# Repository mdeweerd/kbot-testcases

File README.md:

The Makefile is executed in the docker environment as follows:

Using the `setsoft/kicad_auto:dev_k6` image:

```shell
docker compose run --rm dev_k6
```

Using the `setsoft/kicad_auto_test:dev_k6` image:

```shell
docker compose run --rm dev_k7
```

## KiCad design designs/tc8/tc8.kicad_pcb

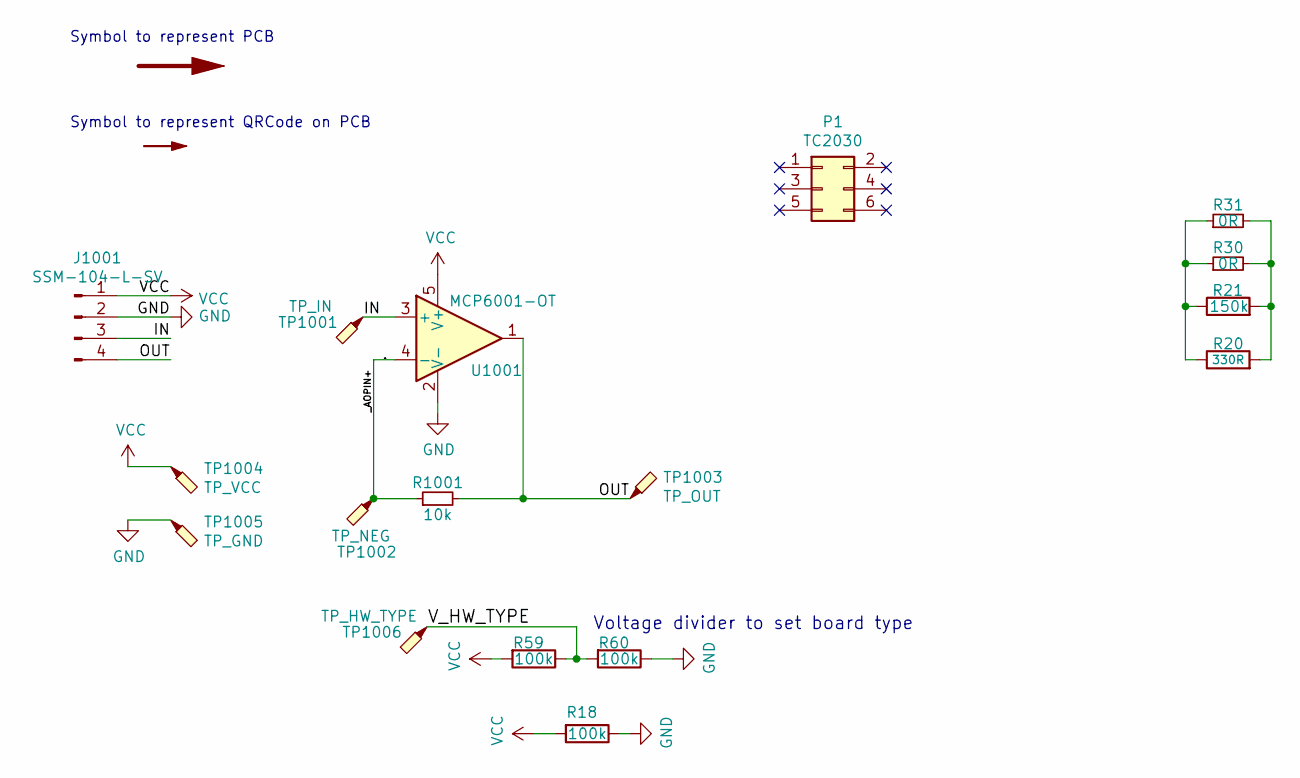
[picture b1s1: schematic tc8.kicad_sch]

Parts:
BRD1: SYM_Arrow_XLarge; biggerPCB
J1001: SSM-104-L-SV; PinSocket_1x04_P2.54mm_Vertical_SMD_Pin1Left
P1: TC2030; TC2030-MCP-FP
QR1: Product QR Code; TC5
R18, R59, R60: 100k; R_0603_1608Metric
R20: 330R; R_0805_2012Metric
R21: 150k; R_0805_2012Metric
R30, R31: 0R; R_0805_2012Metric
R1001: 10k; R_0805_2012Metric
TP1001: TP_IN; TestPoint_Pad_D1.5mm
TP1002: TP_NEG; TestPoint_Pad_D1.5mm
TP1003: TP_OUT; TestPoint_Pad_D1.5mm
TP1004: TP_VCC; TestPoint_Pad_D1.5mm
TP1005: TP_GND; TestPoint_Pad_D1.5mm
TP1006: TP_HW_TYPE; TestPoint_Pad_D1.5mm
U1001: MCP6001-OT; SOT-23-5

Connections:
/IN: J1001.3, TP1001.1, U1001.3 (+)
/OUT: J1001.4, R1001.2, TP1003.1, U1001.1
/V_HW_TYPE: R59.1, R60.2, TP1006.1
/_AOPIN+: R1001.1, TP1002.1, U1001.4 (-)
GND: J1001.2, R18.1, R60.1, TP1005.1, U1001.2 (V-)
unnamed: R20.1, R21.1, R30.1, R31.1
unnamed: R20.2, R21.2, R30.2, R31.2
VCC: J1001.1, R18.2, R59.2, TP1004.1, U1001.5 (V+)

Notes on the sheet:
Voltage divider to set board type
Symbol to represent QRCode on PCB
Symbol to represent PCB

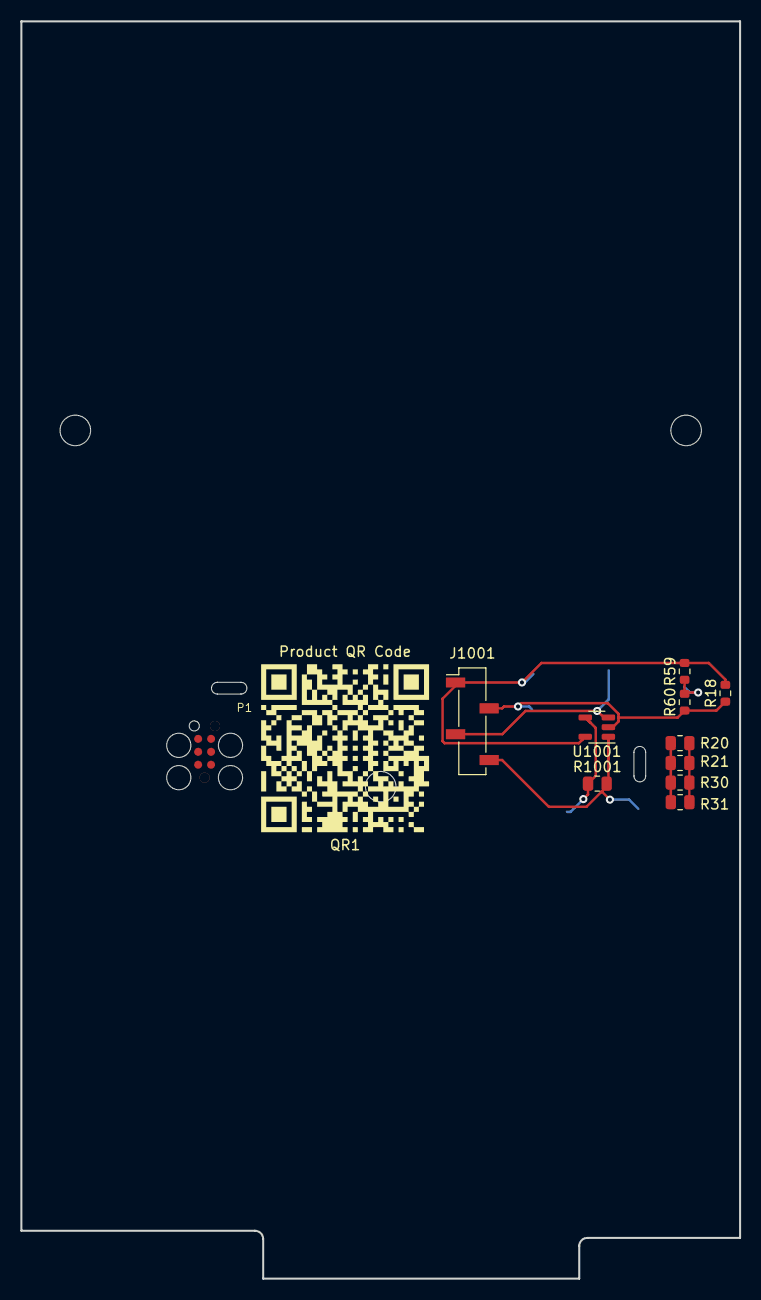
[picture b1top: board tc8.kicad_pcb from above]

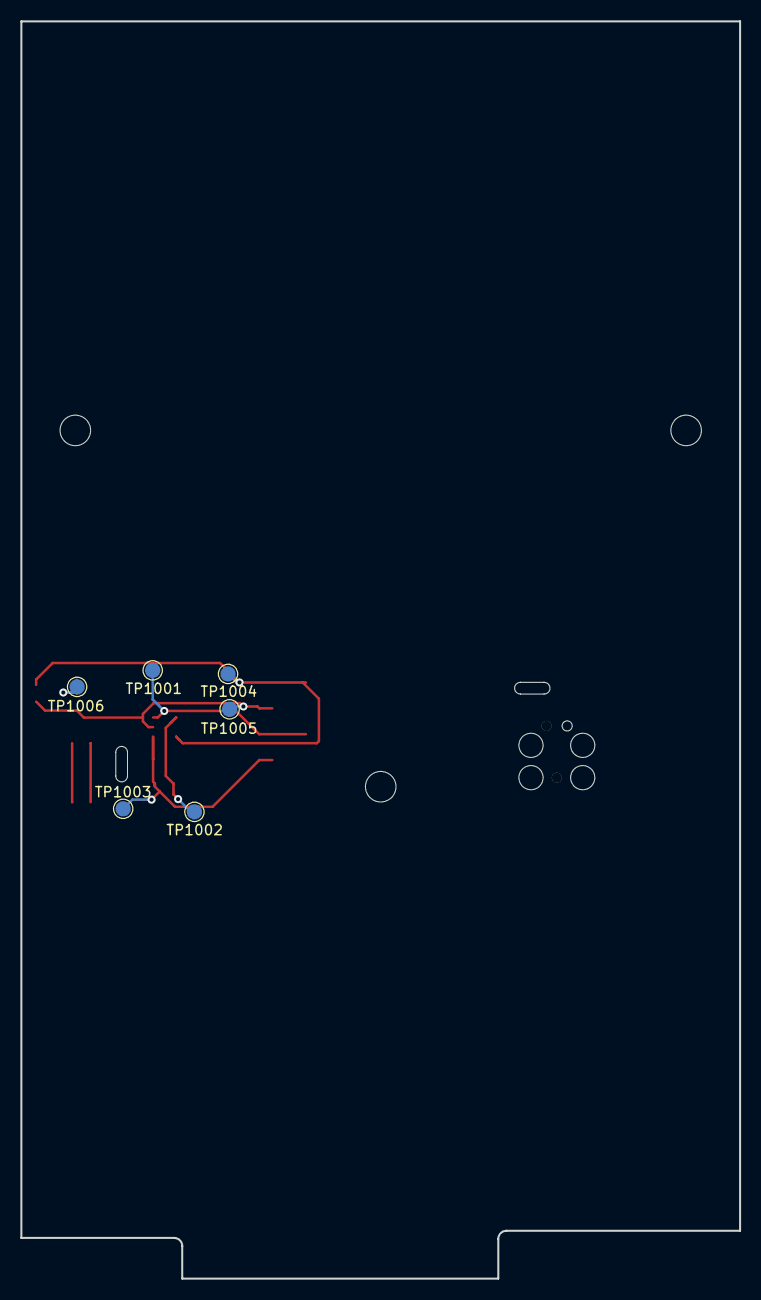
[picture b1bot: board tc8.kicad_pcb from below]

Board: 2 copper layers, 70.6 x 123.5 mm, 19 parts (6 on the bottom side), 8 nets.

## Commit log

2021-11-20 Commit first test case
2021-11-21 Updated testcase to use PCBWay3 samlple
2021-11-21 Setup new testcase
2021-11-21 Prepare packaging tc2
2021-11-21 Update TC to use file from documentation
2021-12-24 Version TC2.md and docs
2021-12-24 Moved old tests to attic
2021-12-24 Commit relevant files
2021-12-29 Improved packaging command
2021-12-30 Added testpoints but then got error
2021-12-30 Including local kibot repo again for docker run
2022-03-17 Add component for board edges, generate report
2022-03-17 Generate all targets
2022-04-20 Addec TC2030 for OAR
2022-12-21 Try comparing variants
2023-02-20 Test cast to get positions for testpoints
2023-02-22 Add resistors to for test
2023-02-22 Ignore vim swaps files
2023-02-22 Add test case where DRC does not detect smaller width
2023-02-28 Convert to teardrop testcase
2023-03-01 Prepare tc6
2023-03-01 Rename to tc6
2023-03-01 Add initial PCB
2023-03-01 Update to kicad6
2023-03-01 Update kibot wrapper
2023-03-01 migrating to version6
2023-03-01 Update lib table
2023-03-01 Ignore less files
2023-03-01 Add docker-compose.yml setup
2023-03-01 Add 3D model
2023-03-01 Add tc7
2023-03-01 Add files needed in git
2023-03-01 Flow corrected using kicad_sch
2023-03-01 Add extra design files
2023-03-01 Finalize test case
2023-03-01 Improve docker compose
2023-03-01 Tag KiCAD 6 version in tc7 directory for diffing
2023-03-01 Add kiboty file again
2023-03-01 Back to kicad7
2023-03-01 Add diff target
2023-03-02 Demonstrate diff issue when PCB changes
2023-03-02 Pull docker compose referenced image before using it
2023-03-02 Makefile
2023-03-02 Add minimal_opt_k7 test case
2023-03-03 Step 1 for Test case demonstrating difference shift based on viewed layers
2023-03-03 Step 2 for Test case demonstrating difference shift based on viewed layers
2023-03-07 Correct TC2030 footprint
2023-03-07 Changed footprint
2023-03-19 Add test case regarding value
2024-04-21 Add tc8
